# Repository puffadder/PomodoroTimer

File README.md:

# Pomodoro Timer

The **Pomodoro Timer** is a timer designed to manage productivity using the Pomodoro Technique.

The work intervals are as follows:

There are three 25-minute work intervals, each separated by a break of 5 mins. After the fourth work session (or *Pomodoro* as I just call it), there is a longer 15 minute break. This cycle continues until the Pomodoro Timer is reset or powered off.

A buzzer goes off after every work or break interval. This can be turned off with a switch.

The LED blinks green if a work interval is starting and it blinks red if a break is starting.

The code is for an ATTiny85 microcontroller. The hardware and PCB design are shown below.

## Contributing
Contributions are welcome! Please follow these steps to contribute:
1. Fork the repository.
2. Create a new branch for your feature or bug fix.
3. Submit a pull request with a clear description of your changes.

## License
This project is licensed under the MIT License. See the [LICENSE](LICENSE) file for details.

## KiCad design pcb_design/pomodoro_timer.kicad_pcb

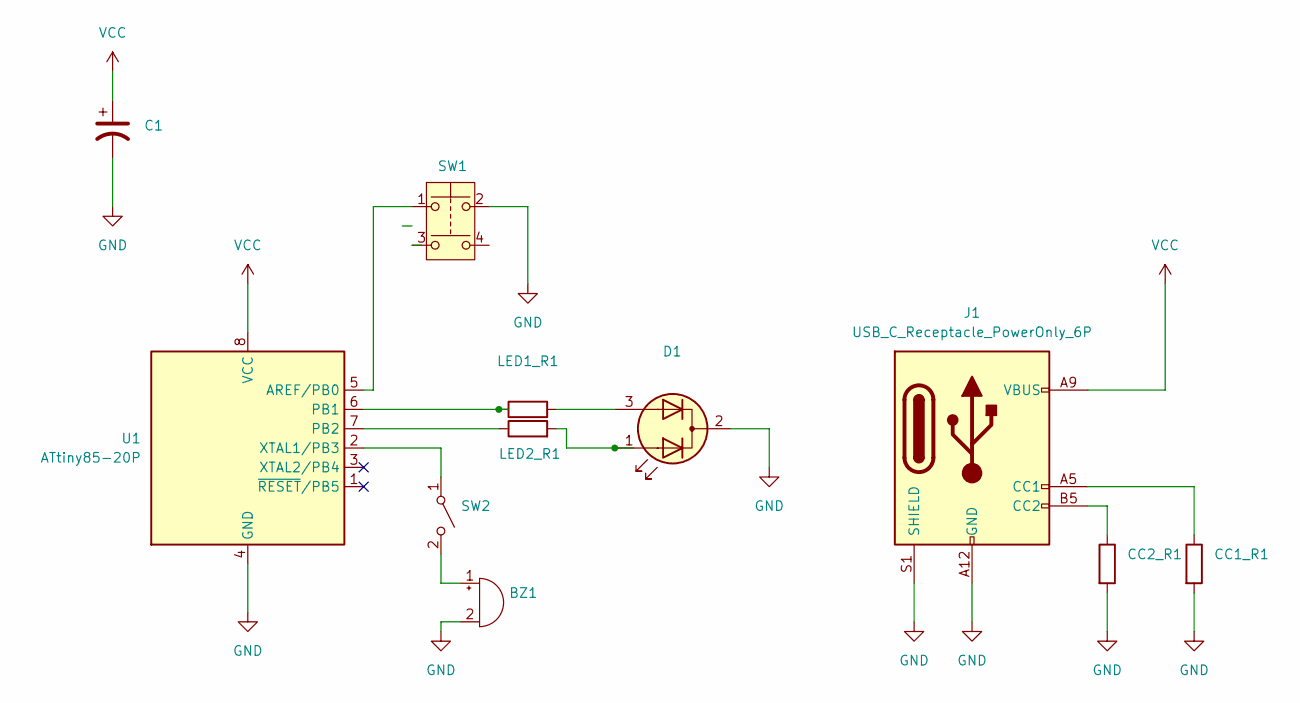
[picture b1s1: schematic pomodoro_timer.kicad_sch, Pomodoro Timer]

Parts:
BZ1: Buzzer; Buzzer_12x9.5RM7.6
C1: C_Polarized_US; C_Disc_D4.3mm_W1.9mm_P5.00mm
CC1_R1, CC2_R1: 5.1K; R_Axial_DIN0207_L6.3mm_D2.5mm_P7.62mm_Horizontal
D1: LED; LED_D3.0mm-3
J1: USB_C_Receptacle_PowerOnly_6P; USB_C_Receptacle_HRO_TYPE-C-31-M-17
LED1_R1, LED2_R1: 220R; R_Axial_DIN0207_L6.3mm_D2.5mm_P7.62mm_Horizontal
SW1: SW_Push_Dual; SW_PUSH-12mm
SW2: SW_SPST; SW_Push_2P2T_Toggle_CK_PVA2xxH4xxxxxxV2
U1: ATtiny85-20P; DIP-8_W7.62mm

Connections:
GND: BZ1.2 (-), C1.2, CC1_R1.2, CC2_R1.2, D1.2 (K), J1.A12 (GND), J1.B12 (GND), J1.S1 (SHIELD), SW1.2, U1.4 (GND)
unnamed: BZ1.1 (+), SW2.2 (B)
unnamed: D1.1 (A1), LED2_R1.2
unnamed: D1.3 (A2), LED1_R1.2
unnamed: CC1_R1.1, J1.A5 (CC1)
unnamed: CC2_R1.1, J1.B5 (CC2)
unnamed: SW2.1 (A), U1.2 (XTAL1/PB3)
unnamed: SW1.1, U1.5 (AREF/PB0)
unnamed: LED1_R1.1, U1.6 (PB1)
unnamed: LED2_R1.1, U1.7 (PB2)
VCC: C1.1, J1.A9 (VBUS), J1.B9 (VBUS), U1.8 (VCC)

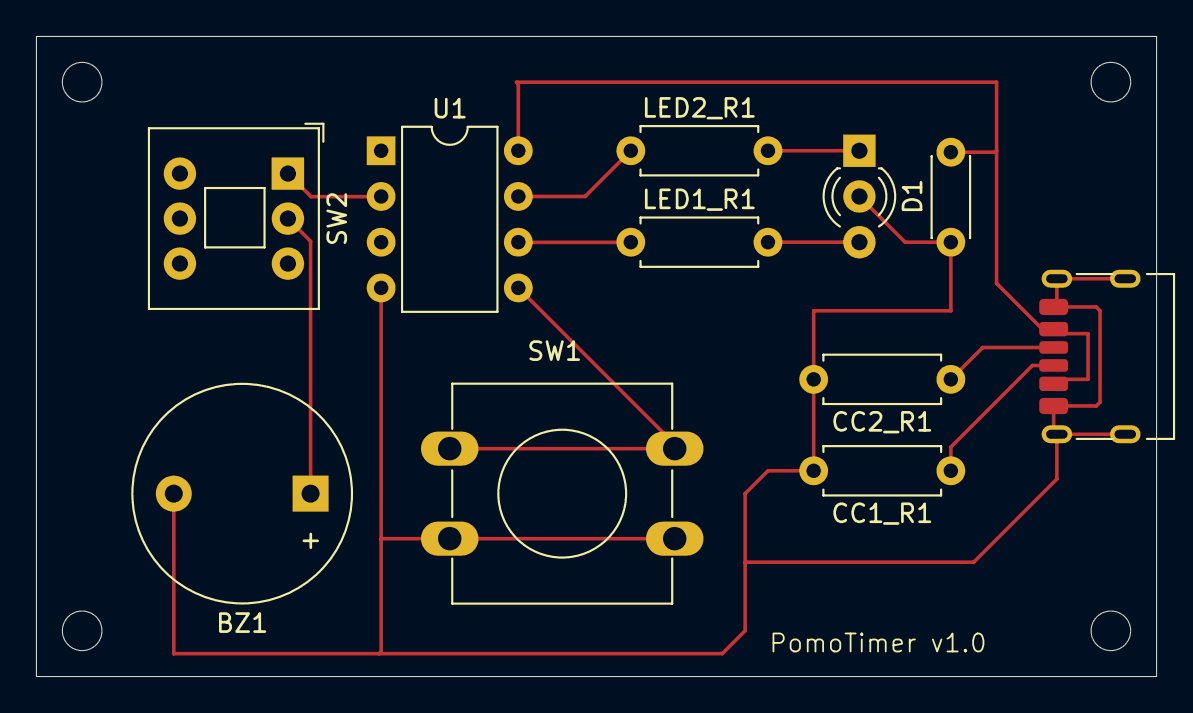
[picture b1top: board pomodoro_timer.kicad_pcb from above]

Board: 2 copper layers, 62.2 x 35.6 mm, 11 parts (0 on the bottom side), 11 nets.

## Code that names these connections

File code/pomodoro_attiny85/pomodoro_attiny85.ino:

#include <avr/io.h>
#include <avr/interrupt.h>
#include <avr/power.h>
#include <avr/sleep.h>
#include <avr/wdt.h>

#define RESET_INTERRUPT

#ifdef RESET_INTERRUPT
#define INTERRUPT_PIN PCINT0 /* Same as PB0 */
#endif

const int redLEDPin = PB1;
const int greenLEDPin = PB2;
const int buzzerPin = PB3;

uint32_t isFirst = 1U;

#ifdef RESET_INTERRUPT
const int resetPin = PB0;
#else
const int resetPin = PB5;
#endif

typedef enum
{
  INIT = 0,
  POMODORO = 1,
  POMODORO_SHORT_BREAK = 2,
  POMODORO_LONG_BREAK = 3,
  INVALID = 4
}PomodoroState;

PomodoroState state = INIT;
uint32_t pomodoroCount = 0U;
uint32_t pomodoroTotalCount = 0U;

const uint32_t clockDiv = 1U; //16U;

const uint32_t numShortBreaks = 3U;

const uint32_t pomodoroOnMs = 1500000U; // 25 minutes
const uint32_t pomodoroShortBreakMs = 300000U; // 5 minutes
const uint32_t pomodoroLongBreakMs = 900000U; // 15 minutes

#ifdef RESET_INTERRUPT
const uint32_t deBounceTimeMs = 200U;

uint32_t numSleeps = 0U;
const uint32_t wakeupTime = 64U;
const uint32_t wdtError = 24U;
extern volatile unsigned long millis_timer_millis;
#endif

volatile uint32_t isReset = 0U;

void setup() {
  //clock_prescale_set(clockDiv_16); /* Make it run at 16.5 / 16 MHz - roughly 1 MHz */

  //Serial.begin(9600);
  pinMode(buzzerPin, OUTPUT);
  pinMode(redLEDPin, OUTPUT);
  pinMode(greenLEDPin, OUTPUT);

#ifdef RESET_INTERRUPT
  cli(); /* Disable interrupts during setup */
  PCMSK |= (1 << INTERRUPT_PIN);    /* Enable ISR for chosen interrupt pin (PCINT1/PB1/pin 6) */
  GIMSK |= (1 << PCIE);             /* Enable PCINT interrupt in the general interrupt mask */
  ADCSRA &= ~ADEN; /* Disable ADC */
  set_sleep_mode(SLEEP_MODE_PWR_DOWN);
  pinMode(resetPin, INPUT_PULLUP);
  sleep_enable();
  sei(); /* Enable interrupts after setup */
#else
  pinMode(A0, INPUT); /* Set PB5 to input */
#endif
}

void loop() { 
  switch (state)
  {
    case INIT:
      state = POMODORO;
      break;
    case POMODORO:
      SignalPomodoroOn();
      SleepMs(pomodoroOnMs);
      if (1U == isReset)
      {
        isReset = 0U;
      }
      else
      {
        pomodoroCount++;
        pomodoroTotalCount++;
        if (pomodoroCount <= numShortBreaks)
        {
          state = POMODORO_SHORT_BREAK;
        }
        else
        {
          state = POMODORO_LONG_BREAK;
        }
      }
      break;
    case POMODORO_SHORT_BREAK:
      SignalPomodoroOff();
      SleepMs(pomodoroShortBreakMs);
      if (1U == isReset)
      {
        isReset = 0U;
      }
      state = POMODORO;
      break;
    case POMODORO_LONG_BREAK:
      //Serial.println("In POMODORO_LONG_BREAK state");
      SignalPomodoroOff();
      SleepMs(pomodoroLongBreakMs);
      if (1U == isReset)
      {
        isReset = 0;
      }
      pomodoroCount = 0U;
      state = POMODORO;
      break;
    default:
      /* Should never come here */
      break;
  }
}

void SignalPomodoroOff()
{
  digitalWrite(greenLEDPin, LOW);

  uint32_t ledBlinkCount = 0U;
  for (ledBlinkCount = 0; ledBlinkCount < 10; ledBlinkCount++)
  {
    digitalWrite(redLEDPin, LOW);
    DelayMs(100U, 1U);
    digitalWrite(redLEDPin, HIGH);
    DelayMs(100U, 1U);
  }

  SoundBuzzer(1U);
}

void SignalPomodoroOn()
{
  digitalWrite(redLEDPin, LOW);

  uint32_t ledBlinkCount = 0U;
  for (ledBlinkCount = 0; ledBlinkCount < 10; ledBlinkCount++)
  {
    DelayMs(100U, 0U);
    digitalWrite(greenLEDPin, LOW);
    DelayMs(100U, 0U);
    digitalWrite(greenLEDPin, HIGH);
  }

  if (1U == isFirst)
  {
    isFirst = 0U;
  }
  else
  {
    SoundBuzzer(1U);
  }
}

void SoundBuzzer(uint32_t breakIfReset)
{
  uint32_t buzzCount = 0;
  for (buzzCount = 0U; (buzzCount < 3U) && (((1U == breakIfReset) && (0U == isReset)) || (0U == breakIfReset)); buzzCount++)
  {
    digitalWrite(buzzerPin, HIGH);
    DelayMs(1000U, breakIfReset);
    digitalWrite(buzzerPin, LOW);
    DelayMs(1000U, breakIfReset);
  }
}

/*
 * @param aWatchdogPrescaler (see wdt.h) can be one of WDTO_15MS, 30, 60, 120, 250, WDTO_500MS, WDTO_1S to WDTO_8S
 *                                                    0 (15 ms) to 3(120 ms), 4 (250 ms) up to 9 (8000 ms)
 */
uint16_t computeSleepMillis(uint8_t aWatchdogPrescaler) {
    uint16_t tResultMillis = 8000;
    for (uint8_t i = 0; i < (9 - aWatchdogPrescaler); ++i) {
        tResultMillis = (tResultMillis / 2);
    }
    return tResultMillis + wakeupTime; // + 64 for the startup time
}

/*
 * @param aWatchdogPrescaler (see wdt.h) can be one of WDTO_15MS, 30, 60, 120, 250, WDTO_500MS, WDTO_1S to WDTO_8S
 * @param aAdjustMillis if true, adjust the Arduino internal millis counter the get quite correct millis() 
 * results even after sleep, since the periodic 1 ms timer interrupt is disabled while sleeping.
 */
void sleepWithWatchdog(uint8_t aWatchdogPrescaler, bool aAdjustMillis) {
    MCUSR = 0; // Clear MCUSR to enable a correct interpretation of MCUSR after reset

    // use wdt_enable() since it handles that the WDP3 bit is in bit 5 of the WDTCR register
    wdt_enable(aWatchdogPrescaler);
    WDTCR |= _BV(WDIE) | _BV(WDIF); // Watchdog interrupt enable + reset interrupt flag -> needs ISR(WDT_vect)
    sei();         // Enable interrupts
    sleep_cpu();   // The watchdog interrupt will wake us up from sleep

    // We wake up here :-)
    wdt_disable(); // Because next interrupt will otherwise lead to a reset, since wdt_enable() sets WDE / Watchdog System Reset Enable
    /*
     * Since timer clock may be disabled adjust millis only if not slept in IDLE mode (SM2...0 bits are 000)
     */
    if (aAdjustMillis && (MCUCR & ((_BV(SM1) | _BV(SM0)))) != 0) {
        millis_timer_millis += computeSleepMillis(aWatchdogPrescaler);
    }
}

void SleepMs(uint32_t sleepTimeMs)
{
  uint32_t totalTimeMs = 0U;

  while (0U == isReset)
  {
    sleepWithWatchdog(WDTO_1S, false);
    totalTimeMs += (1000U + wdtError + wakeupTime);

    if (totalTimeMs >= sleepTimeMs)
    {
      break;
    }
  }
}

void DelayMs(uint32_t delayMs, uint32_t breakIfReset)
{
  uint32_t prevTime = millis();
  delayMs = delayMs / clockDiv;

  while (1)
  {
    uint32_t currTime = millis();
    if (((1U == breakIfReset) && (1U == isReset)) || ((currTime - prevTime) >= delayMs))
    {
      break;
    }
  }
}

#ifdef RESET_INTERRUPT
ISR(PCINT0_vect)
{
  static uint32_t lastInterruptTime = 0U;
  uint32_t currInterruptTime = millis();
  /* If interrupts come faster than 200ms, assume it's a bounce and ignore */
  if ((currInterruptTime - lastInterruptTime) > deBounceTimeMs)
  {
    isReset = 1U;
  }
  lastInterruptTime = currInterruptTime;
}

ISR(WDT_vect) {
    numSleeps++;
}
#endif

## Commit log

2025-02-04 folder structure update
2025-02-19 updated pins for connections
2025-03-03 changed busy loop to sleep
2025-03-03 Create LICENSE
2025-08-08 Update LICENSE
2025-08-08 don't sound buzzer when powering on
2025-08-08 Images for schematic and PCB design
